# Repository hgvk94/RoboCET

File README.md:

# RoboCET
This repository contains the source code and schematics for the quadcopter workshop conducted by RoboCET in September 2015. 

The source code depends on the following hardware : Arduino Pro mini microcontroller board MPU 6050 accelerometer+Gyroscope Electronic Speed controller units 6 channel receiver

The following libraries are also required : I2CdevLib (https://github.com/jrowberg/i2cdevlib/blob/master/Arduino/MPU6050/MPU6050_6Axis_MotionApps20.h)

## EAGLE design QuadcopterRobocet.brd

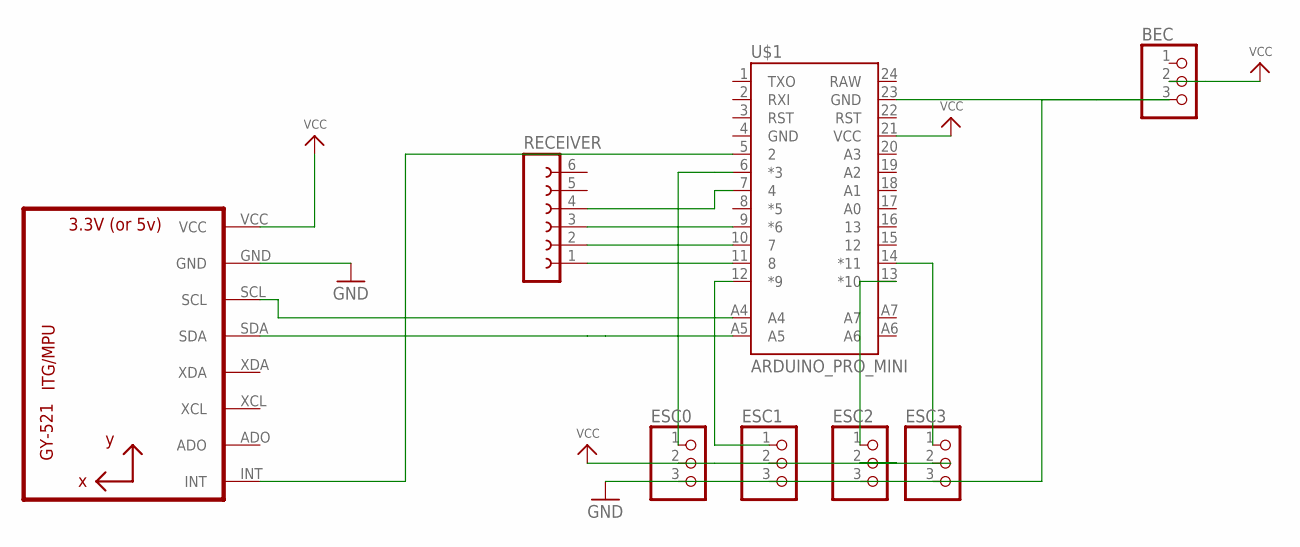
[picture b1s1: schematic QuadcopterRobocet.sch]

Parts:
BEC: PINHD-1X3; 1X03
ESC0, ESC1, ESC2, ESC3: PINHD-1X3; 1X03
RECEIVER: FE06-1; FE06
U1: GY-521MPU6050; GY-521
U$1: ARDUINO_PRO_MINI

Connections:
GND: BEC.3, ESC0.3, ESC1.3, ESC2.3, ESC3.3, U1.GND, U$1.23 (GND)
unnamed: U1.SCL, U$1.A4
unnamed: U1.SDA, U$1.A5
unnamed: U1.INT, U$1.5 (2)
unnamed: RECEIVER.1, U$1.11 (8)
unnamed: RECEIVER.2, U$1.10 (7)
unnamed: RECEIVER.3, U$1.9 (*6)
unnamed: RECEIVER.4, U$1.7 (4)
unnamed: ESC0.1, U$1.6 (*3)
unnamed: ESC1.1, U$1.12 (*9)
unnamed: ESC2.1, U$1.13 (*10)
unnamed: ESC3.1, U$1.14 (*11)
VCC: BEC.2, ESC0.2, ESC1.2, ESC2.2, ESC3.2, U1.VCC, U$1.21 (VCC)

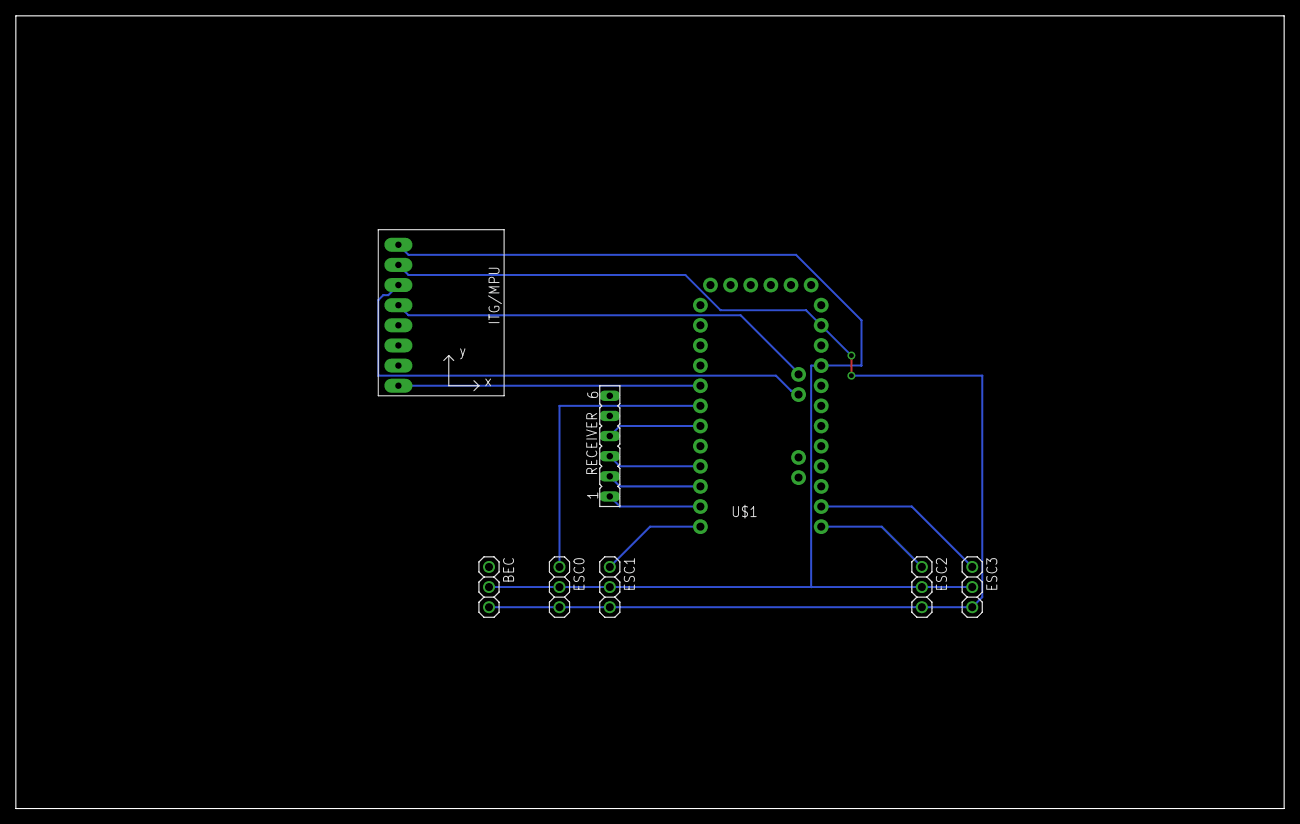
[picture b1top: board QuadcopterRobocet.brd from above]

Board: 2 copper layers, 160.0 x 100.0 mm, 8 parts (0 on the bottom side), 13 nets.

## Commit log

2017-01-28 Added Schematic files

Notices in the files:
parts and their libraries:
SparkFun-Boards: Licensing: Creative Commons ShareAlike 4.0 International - https://creativecommons.org/licenses/by-sa/4.0
microbuilder: This work is placed in the public domain, and may be freely used for commercial and non-commercial work with the following conditions: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
